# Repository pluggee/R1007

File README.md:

# R1007
Quad 20A DC Low Side NFET Control Switches
License
-------
R1007 is released under the GNU GPL v3, which you can find at <http://www.gnu.org/licenses/gpl-3.0.en.html>,
Check License.md for more details.

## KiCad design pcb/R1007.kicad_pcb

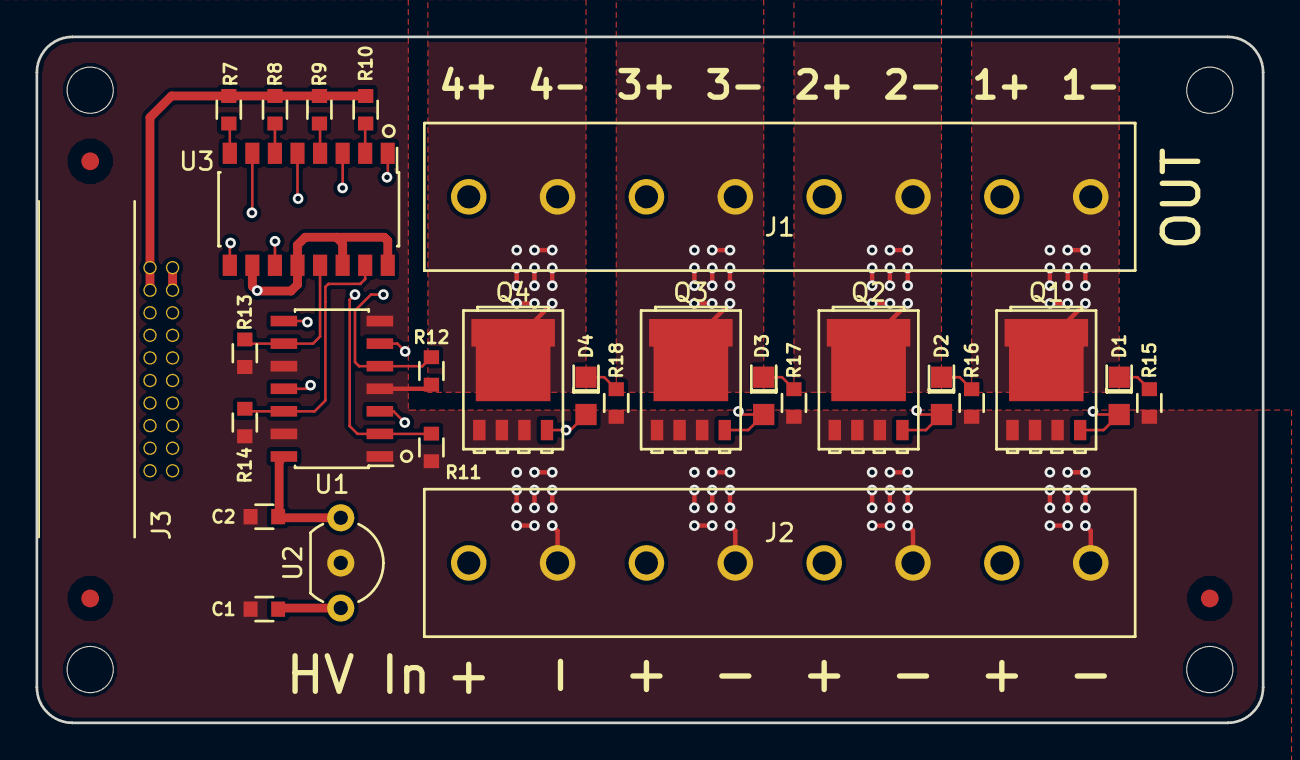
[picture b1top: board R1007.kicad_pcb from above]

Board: 4 copper layers, 69.0 x 38.6 mm, 36 parts (1 on the bottom side), 29 nets.

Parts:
A1: ART; pluggeeLabsIcon-13X7
C1, C2: CC0603KRX7R9BB104; CAPC0603
D1, D2, D3, D4: LTW-170TK; DIOC200X120X110
FID1, FID2, FID3: FIDTOP001
J1, J2: CONN500P-01X08
J3: CONN_R1000A_EXTENSION; CONN127P-02X10
MP1, MP2, MP3, MP4: MECH_NPTH_M3
Q1, Q2, Q3, Q4: PSMN1R2-30YLC; SOT127P500X110-5
R7, R8, R9, R10, R15, R16, R17, R18: RC0603FR-071KL; RESC0603
R11, R12, R13, R14: RC0603FR-074K7L; RESC0603
U1: 74HC125; SOIC127P870X390X175-14
U2: AS78L05ZTR-E1; TO92_AMMO
U3: TLP293-4; SOIC127P1030X455X210-16

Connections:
+5P: C2.1, U1.14, U2.1, U3.10, U3.12, U3.14, U3.16
/GN1: D1.2, Q1.4, U1.11
/GN2: D2.2, Q2.4, U1.8
/GN3: D3.2, Q3.4, U1.6
/GN4: D4.2, Q4.4, U1.3
/IGN1: R14.1, U1.12, U3.15
/IGN2: R13.1, U1.9, U3.13
/IGN3: R12.1, U1.5, U3.11
/IGN4: R11.1, U1.2, U3.9
/INR1: R10.1, U3.2
/INR2: R9.1, U3.4
/INR3: R8.1, U3.6
/INR4: R7.1, U3.8
/N1: J1.1, Q1.5
/N2: J1.3, Q2.5
/N3: J1.5, Q3.5
/N4: J1.7, Q4.5
GND: J3.18, J3.20, R7.2, R8.2, R9.2, R10.2
GNDPWR: C1.2, C2.2, J2.2, J2.4, J2.6, J2.8, Q1.1, Q1.2, Q1.3, Q2.1, Q2.2, Q2.3, Q3.1, Q3.2, Q3.3, Q4.1, Q4.2, Q4.3, R11.2, R12.2, R13.2, R14.2, R15.2, R16.2, R17.2, R18.2, U1.1, U1.4, U1.7, U1.10, U1.13, U2.2
HT: J3.17, J3.19
unnamed: D1.1, R15.1
unnamed: D2.1, R16.1
unnamed: D3.1, R17.1
unnamed: D4.1, R18.1
PX1: J3.13, U3.1
PX2: J3.11, U3.3
PX3: J3.9, U3.5
PX4: J3.7, U3.7
VDD: C1.1, J1.2, J1.4, J1.6, J1.8, J2.1, J2.3, J2.5, J2.7, U2.3

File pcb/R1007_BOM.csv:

Reference;Quantity;Value;Footprint;Datasheet;Manufacturer;MPN;SKU;Color;Res;Tol;Pwr;C;Vmax;Type
A1 ;1;ART;pluggee:pluggeeLabsIcon-13X7;
C1 C2 ;2;CC0603KRX7R9BB104;Main:CAPC0603;;Yageo;CC0603KRX7R9BB104;STUFF;;;±10%;;100 nF;50.0V;X7R
D1 D2 D3 D4 ;4;LTW-170TK;Main:DIOC200X120X110;;Lite-On Inc.;LTW-170TK;COMMON;WHITE;;;;;;
FID1 FID2 FID3 ;3;FIDTOP001;Main:FIDTOP001;
J1 J2 ;2;CONN500P-01X08;Main:CONN500P-01X08;;Phoenix Contact;1935226;STUFF;;;;;;;
J3 ;1;CONN_R1000A_EXTENSION;Main:CONN127P-02X10;;CNC Tech;3221-20-0200-00;STUFF;;;;;;;
MP1 MP2 MP3 MP4 ;4;MECH_NPTH_M3;Main:MECH_NPTH_M3;
Q1 Q2 Q3 Q4 ;4;PSMN1R2-30YLC;Main:SOT127P500X110-5;;NXP Semiconductors;PSMN1R2-30YLC,115;STUFF;;;;;;;
R11 R12 R13 R14 ;4;RC0603FR-074K7L;Main:RESC0603;;Yageo;RC0603FR-074K7L;STUFF;;4.7 kΩ;±1%;100 mW;;;
R10 R15 R16 R17 R18 R7 R8 R9 ;8;RC0603FR-071KL;Main:RESC0603;;Yageo;RC0603FR-071KL;STUFF;;1.00 kΩ;±1%;100 mW;;;
U1 ;1;74HC125;Main:SOIC127P870X390X175-14;;NXP Semiconductors;74HC125D,653;STUFF;;;;;;;
U2 ;1;AS78L05ZTR-E1;Main:TO92_AMMO;;Diodes Incorporated;AS78L05ZTR-E1;STUFF;;;;;;;
U3 ;1;TLP293-4;Main:SOIC127P1030X455X210-16;;Toshiba Semiconductor and Storage;TLP293-4(GB-TP,E;STUFF;;;;;;;

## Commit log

2016-07-25 added doc readme
2016-07-26 added R1007 pcb
2016-07-28 wip, need to add 74 buffers and LEDs
2016-07-28 added netlist
2016-07-29 released first version
2016-07-29 fixed 50A to 20A
2016-08-19 added BOM
2017-02-02 added license
2017-04-02 completed layout, wip
2017-04-16 pushing first public release
2017-04-16 regnerated BOM
2017-04-25 separated +ve supplies and moved LEDs to board edge
